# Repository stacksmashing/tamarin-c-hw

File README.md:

# Tamarin-C Hardware

This is the PCB for the [Tamarin-C firmware](https://github.com/stacksmashing/tamarin-c).

A tool to explore USB-C on Apple devices using the [Tamarin C Hardware](https://github.com/stacksmashing/tamarin-c-hw).

It is based on the [Central Scrutinizer by Marc Zyngier](https://git.kernel.org/pub/scm/linux/kernel/git/maz/cs-hw.git/).

If you're assembling one: An interactive BOM is included with this repository.

## License

This hardware is licensed under [CC BY-NC](https://creativecommons.org/licenses/by-nc/4.0/) - the Creative Commons Attribution-NonCommercial 4.0 International liecnse.

## Thanks

[Aisler](https://aisler.net) was nice enough to make a last-minute run for 37c3 possible, and additionally sponsored a hundred PCBs to give out at the conference. Thanks a lot!

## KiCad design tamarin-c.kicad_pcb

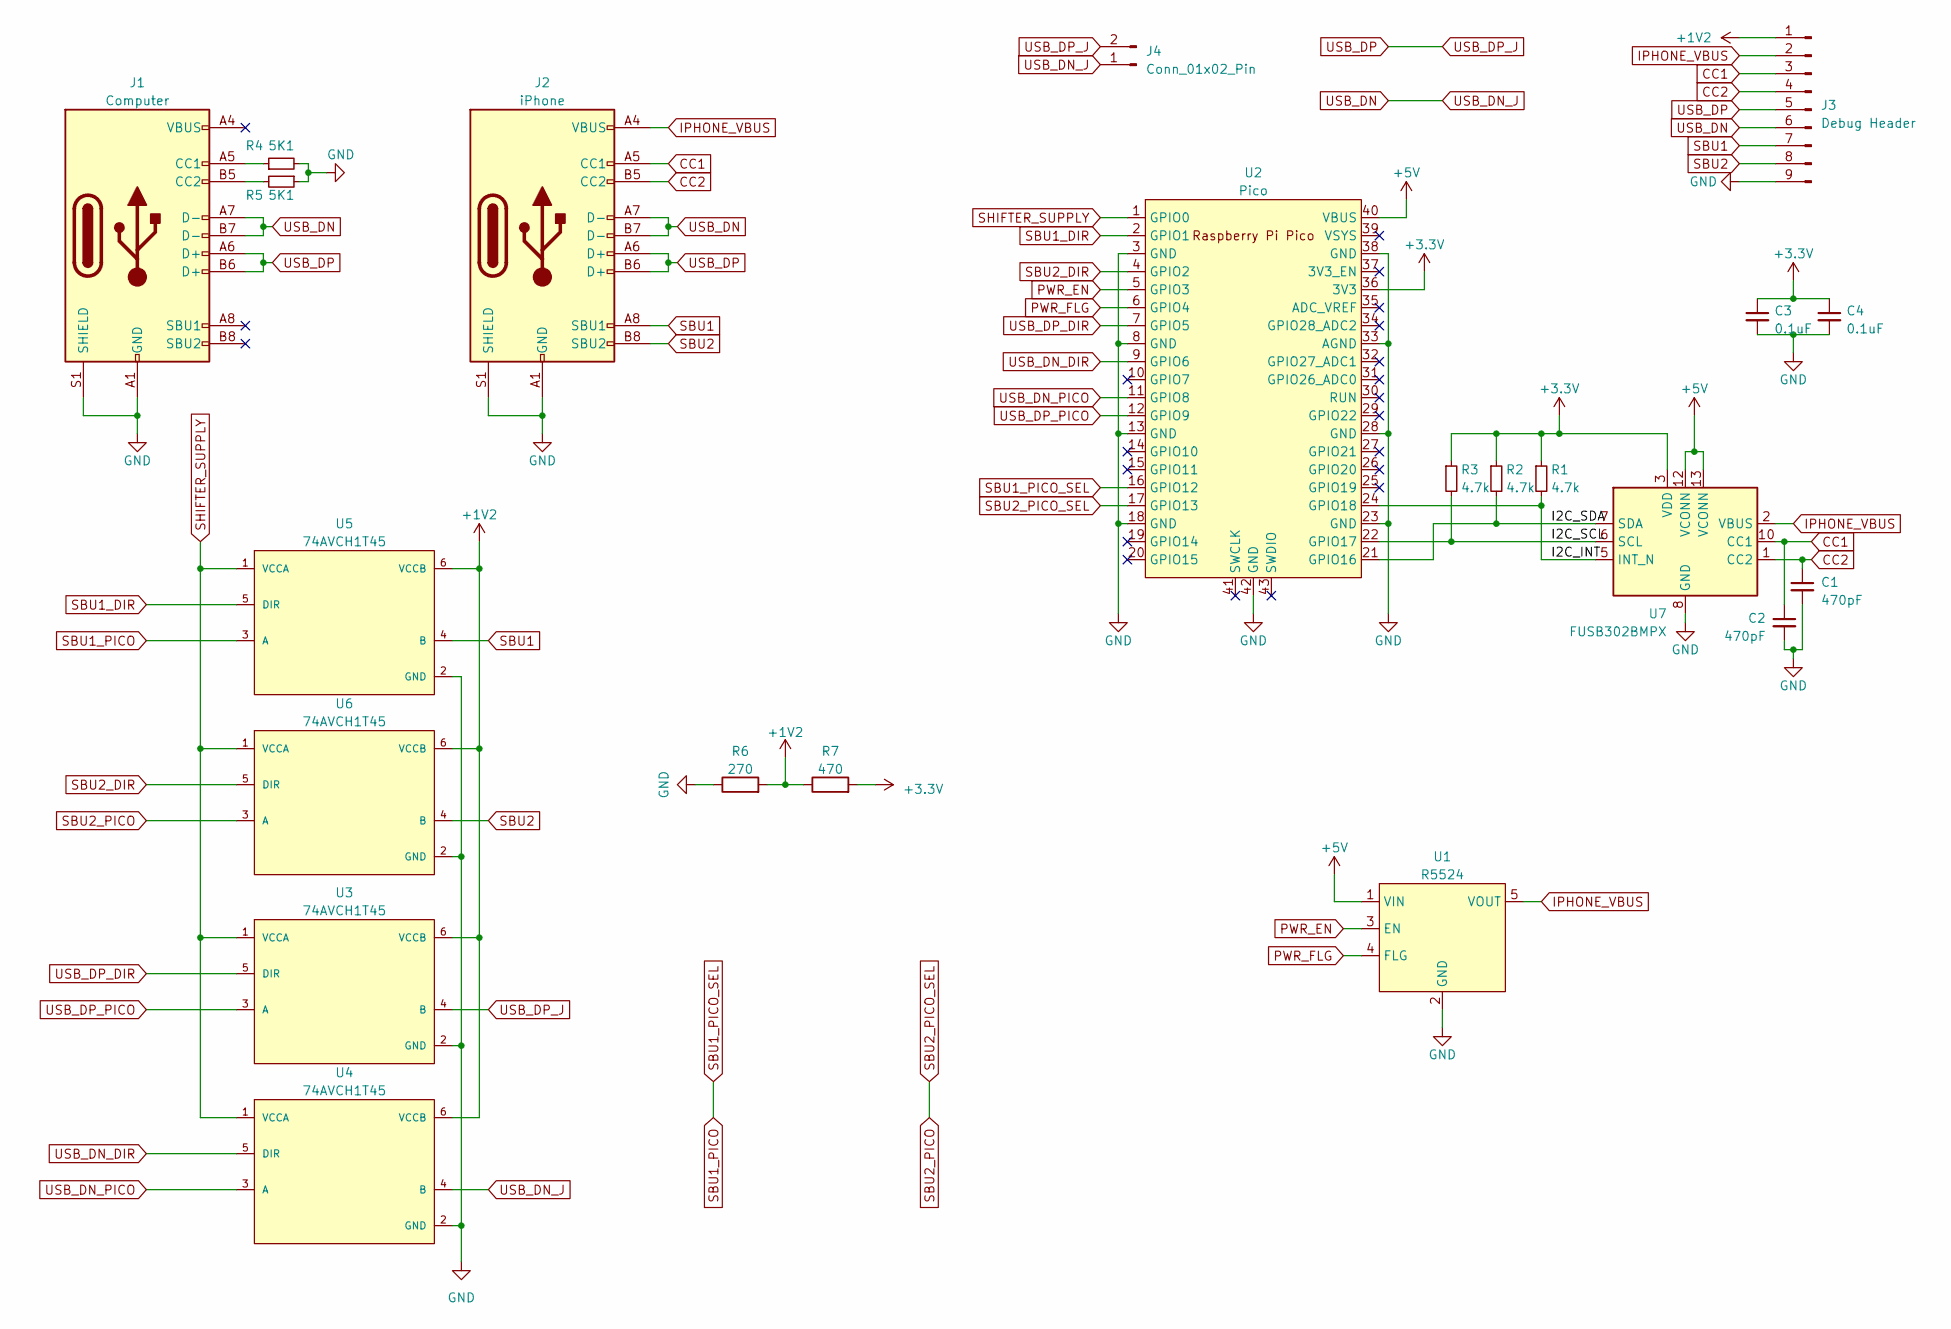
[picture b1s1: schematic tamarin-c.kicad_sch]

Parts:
C1, C2: 470pF; C_0603_1608Metric
C3, C4: 0.1uF; C_0603_1608Metric; LCSC C1525
J1: Computer; USB_C_Receptacle_HRO_TYPE-C-31-M-12
J2: iPhone; USB_C_Receptacle_HRO_TYPE-C-31-M-12
J3: Debug Header; PinHeader_1x09_P2.54mm_Vertical
J4: Conn_01x02_Pin; PinHeader_1x02_P2.54mm_Vertical
R1, R2, R3: 4.7k; R_0603_1608Metric
R4, R5: 5K1; R_0603_1608Metric
R6: 270; R_0603_1608Metric; LCSC C138294
R7: 470; R_0603_1608Metric; LCSC C25117
U1: R5524; TSOT-23-5; DigiKey 2129-R5524N004A-TR-FECT-ND
U2: Pico; RPi_Pico_SMD_TH
U3, U4, U5, U6: 74AVCH1T45; SOT-23-6; mouser part number 595-SN74AVCH1T45DCKT; digikey description IC TRNSLTR BIDIRECTIONAL SC70-6
U7: FUSB302BMPX; WQFN-14-1EP_2.5x2.5mm_P0.5mm_EP1.45x1.45mm

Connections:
+1V2: J3.1, R6.2, R7.1, U3.6 (VCCB), U4.6 (VCCB), U5.6 (VCCB), U6.6 (VCCB)
+3.3V: C3.1, C4.1, R1.1, R2.1, R3.1, R7.2, U2.36 (3V3), U7.3 (VDD), U7.4 (VDD)
+5V: U1.1 (VIN), U2.40 (VBUS), U7.12 (VCONN), U7.13 (VCONN)
/I2C_INT: R1.2, U2.24 (GPIO18), U7.5 (INT_N)
/I2C_SCL: R3.2, U2.22 (GPIO17), U7.6 (SCL)
/I2C_SDA: R2.2, U2.21 (GPIO16), U7.7 (SDA)
CC1: C2.1, J2.A5 (CC1), J3.3, U7.10 (CC1), U7.11 (CC1)
CC2: C1.1, J2.B5 (CC2), J3.4, U7.1 (CC2), U7.14 (CC2)
GND: C1.2, C2.2, C3.2, C4.2, J1.A1 (GND), J1.A12 (GND), J1.B1 (GND), J1.B12 (GND), J1.S1 (SHIELD), J2.A1 (GND), J2.A12 (GND), J2.B1 (GND), J2.B12 (GND), J2.S1 (SHIELD), J3.9, R4.2, R5.1, R6.1, U1.2 (GND), U2.3 (GND), U2.8 (GND), U2.13 (GND), U2.18 (GND), U2.23 (GND), U2.28 (GND), U2.33 (AGND), U2.38 (GND), U2.42 (GND), U3.2 (GND), U4.2 (GND), U5.2 (GND), U6.2 (GND), U7.8 (GND), U7.9 (GND), U7.15 (GND); also elsewhere on the board
IPHONE_VBUS: J2.A4 (VBUS), J2.A9 (VBUS), J2.B4 (VBUS), J2.B9 (VBUS), J3.2, U1.5 (VOUT), U7.2 (VBUS)
unnamed 10: J1.A5 (CC1), R4.1; also elsewhere on the board
unnamed: J1.B5 (CC2), R5.2
PWR_EN: U1.3 (EN), U2.5 (GPIO3)
PWR_FLG: U1.4 (FLG), U2.6 (GPIO4)
SBU1: J2.A8 (SBU1), J3.7, U5.4 (B)
SBU1_DIR: U2.2 (GPIO1), U5.5 (DIR)
SBU1_PICO: U2.16 (GPIO12), U5.3 (A)
SBU2: J2.B8 (SBU2), J3.8, U6.4 (B)
SBU2_DIR: U2.4 (GPIO2), U6.5 (DIR)
SBU2_PICO: U2.17 (GPIO13), U6.3 (A)
SHIFTER_SUPPLY: U2.1 (GPIO0), U3.1 (VCCA), U4.1 (VCCA), U5.1 (VCCA), U6.1 (VCCA)
USB_DN: J1.A7 (D-), J1.B7 (D-), J2.A7 (D-), J2.B7 (D-), J3.6, J4.1, U4.4 (B)
USB_DN_DIR: U2.9 (GPIO6), U4.5 (DIR)
USB_DN_PICO: U2.11 (GPIO8), U4.3 (A)
USB_DP: J1.A6 (D+), J1.B6 (D+), J2.A6 (D+), J2.B6 (D+), J3.5, J4.2, U3.4 (B)
USB_DP_DIR: U2.7 (GPIO5), U3.5 (DIR)
USB_DP_PICO: U2.12 (GPIO9), U3.3 (A)

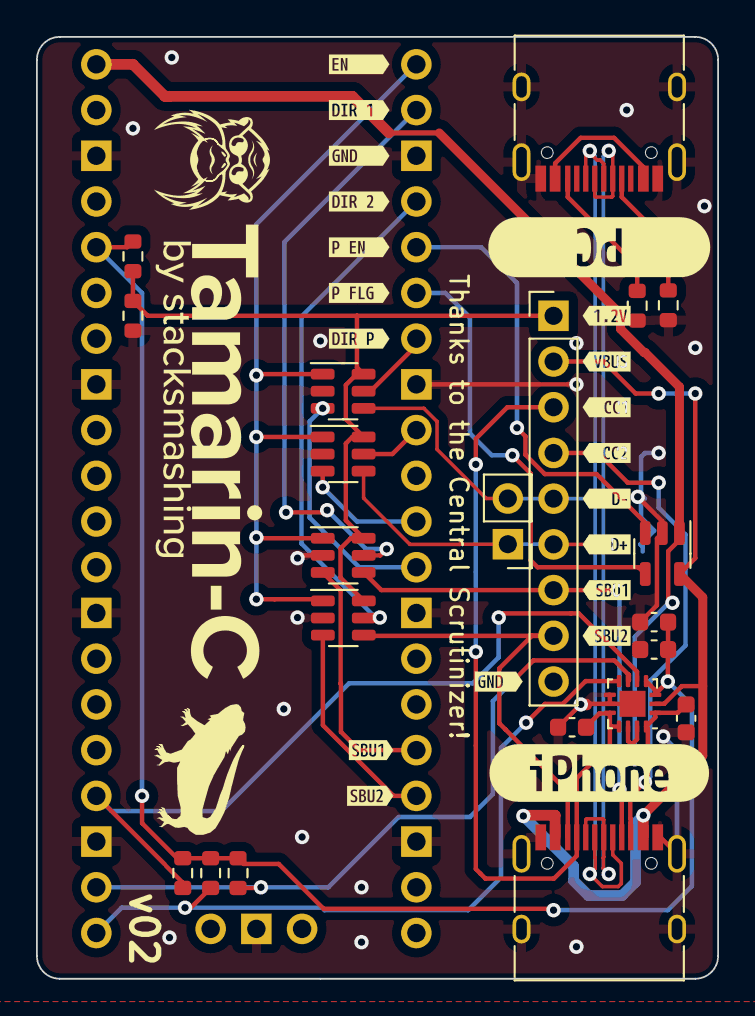
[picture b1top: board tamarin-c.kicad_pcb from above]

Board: 2 copper layers, 37.8 x 52.3 mm, 42 parts (1 on the bottom side), 27 nets.

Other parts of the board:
Re: 5K1; R_0603_1608Metric
kibuzzard-656E4D9B: G***; kibuzzard-656E4D9B
kibuzzard-656E4D96: G***; kibuzzard-656E4D96
kibuzzard-656E47A2: G***; kibuzzard-656E47A2
kibuzzard-656E47C5: G***; kibuzzard-656E47C5
kibuzzard-656E47CA: G***; kibuzzard-656E47CA
kibuzzard-656E48C1: G***; kibuzzard-656E48C1
kibuzzard-656E48C5: G***; kibuzzard-656E48C5
kibuzzard-656E48C9: G***; kibuzzard-656E48C9
kibuzzard-656E48CC: G***; kibuzzard-656E48CC
kibuzzard-656E48CF: G***; kibuzzard-656E48CF
kibuzzard-656E48D3: G***; kibuzzard-656E48D3
kibuzzard-656E48D7: G***; kibuzzard-656E48D7
kibuzzard-656E48DB: G***; kibuzzard-656E48DB
kibuzzard-656E51B5: G***; kibuzzard-656E51B5
kibuzzard-656E51BD: G***; kibuzzard-656E51BD
kibuzzard-656E479E: G***; kibuzzard-656E479E
kibuzzard-656E4785: G***; kibuzzard-656E4785
kibuzzard-656E4795: G***; kibuzzard-656E4795
kibuzzard-657EFD91: G***; kibuzzard-657EFD91
kibuzzard-657F00AC: G***; kibuzzard-657F00AC

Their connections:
GND: Re.2; also elsewhere on the board
unnamed 10: Re.1; also elsewhere on the board

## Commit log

2023-12-28 Initial public release
2023-12-30 Update README.md to fix Central Scrutinizer link
